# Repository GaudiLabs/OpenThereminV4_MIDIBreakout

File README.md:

BreakOut board for the OpenTheremin V4.5 (featuring a 10 pin break out connector).
- MIDI DIN Connector
- Main Signals on soldering tabs (+5V / GND / AUDIO / CV1 / CV2 / GATE / TXD / RXD / RESET / GND)
- Use a 2x5pin, 1.27mm pitch jumper cable to connect to main board
- Upload the OpenTheremin V4 MIDI software
- Build into custom design case or print the OpenTheremin MIDI port case from the STL file.

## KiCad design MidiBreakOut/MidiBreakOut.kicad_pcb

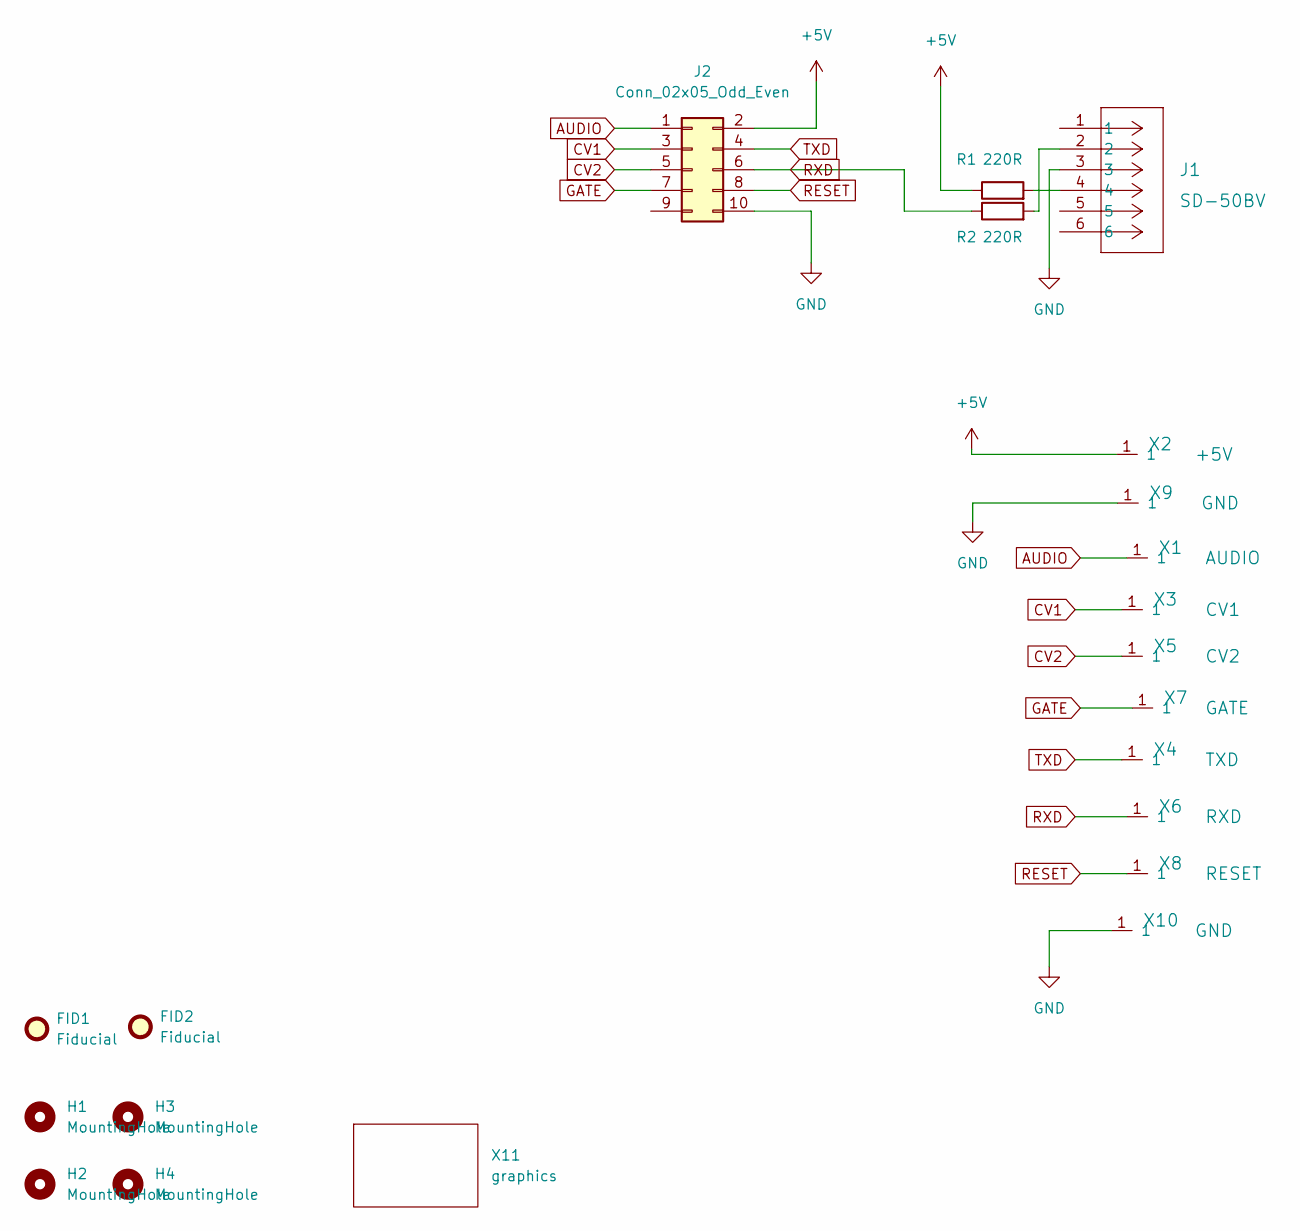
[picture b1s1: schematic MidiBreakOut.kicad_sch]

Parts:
FID1, FID2: Fiducial; Fiducial_1mm_Dia_2.54mm_Outer_CopperBottom
H1, H2, H3, H4: MountingHole; MountingHole_3.2mm_M3
J1: SD-50BV; CONN6_SD-50BV_CUD
J2: Conn_02x05_Odd_Even; OTBreakOut_2x05_P1.27mm_Vertical_SMD
R1, R2: 220R; R_0805_2012Metric
X1: AUDIO; PAD_SMD_4x2mm_ThroughHole
X2: +5V; PAD_SMD_4x2mm_ThroughHole
X3: CV1; PAD_SMD_4x2mm_ThroughHole
X4: TXD; PAD_SMD_4x2mm_ThroughHole
X5: CV2; PAD_SMD_4x2mm_ThroughHole
X6: RXD; PAD_SMD_4x2mm_ThroughHole
X7: GATE; PAD_SMD_4x2mm_ThroughHole
X8: RESET; PAD_SMD_4x2mm_ThroughHole
X9, X10: GND; PAD_SMD_4x2mm_ThroughHole
X11: graphics; BreakOut

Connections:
+5V: J2.2, R1.1, X2.1
AUDIO: J2.1, X1.1
CV1: J2.3, X3.1
CV2: J2.5, X5.1
GATE: J2.7, X7.1
GND: J1.3, J2.10, X9.1, X10.1
unnamed: J1.2, R2.2
unnamed: J1.4, R1.2
RESET: J2.8, X8.1
RXD: J2.6, R2.1, X6.1
TXD: J2.4, X4.1

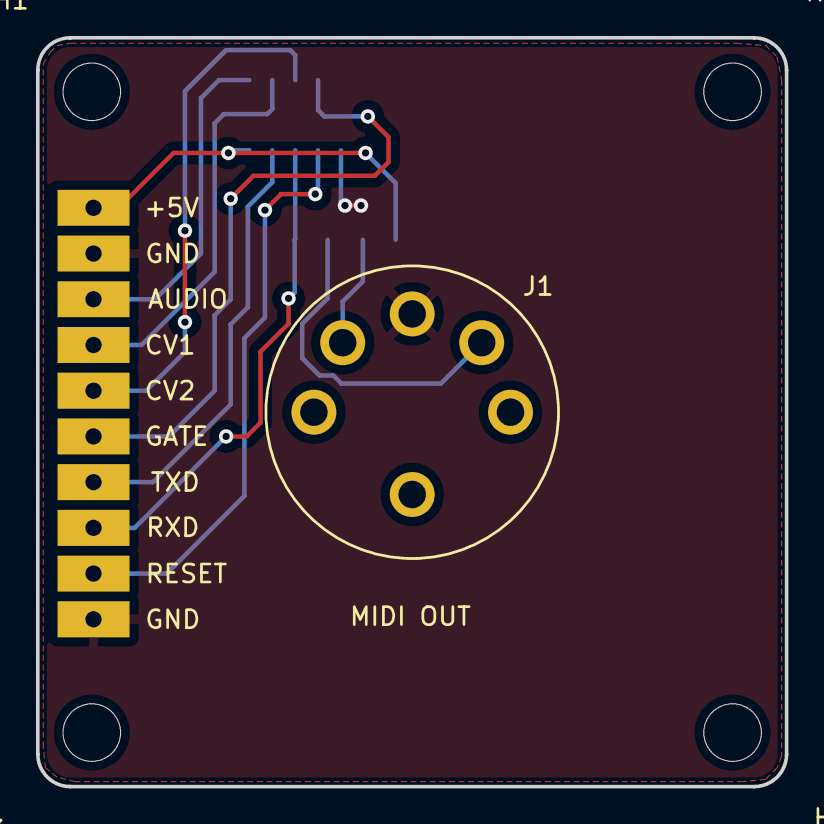
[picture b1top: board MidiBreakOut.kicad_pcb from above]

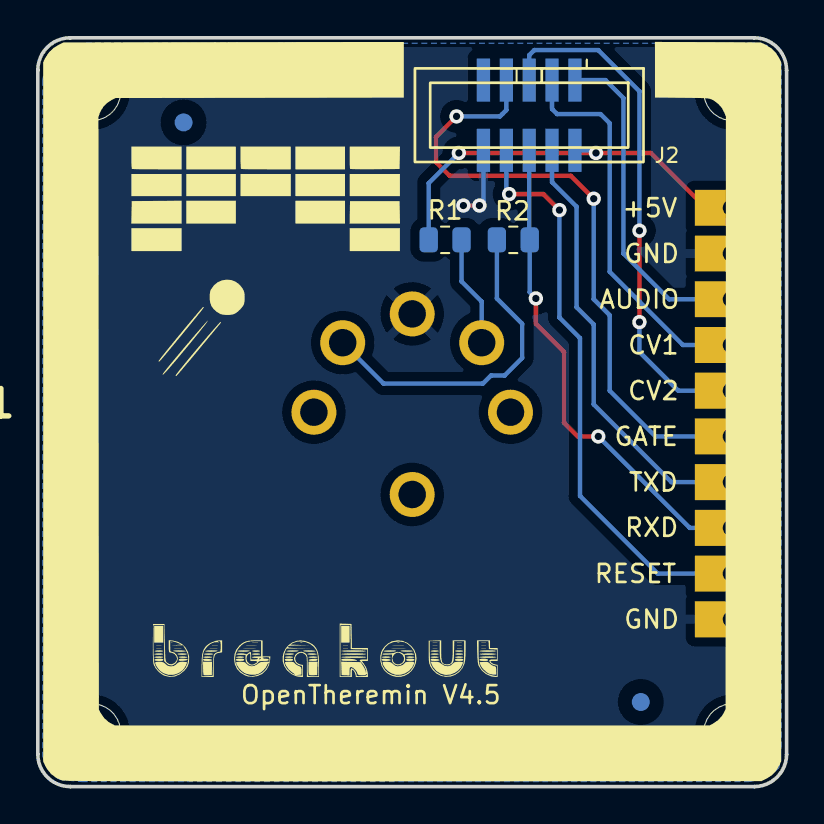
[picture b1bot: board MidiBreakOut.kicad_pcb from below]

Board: 2 copper layers, 41.6 x 41.6 mm, 21 parts (15 on the bottom side), 11 nets.

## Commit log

2025-11-10 First Release
